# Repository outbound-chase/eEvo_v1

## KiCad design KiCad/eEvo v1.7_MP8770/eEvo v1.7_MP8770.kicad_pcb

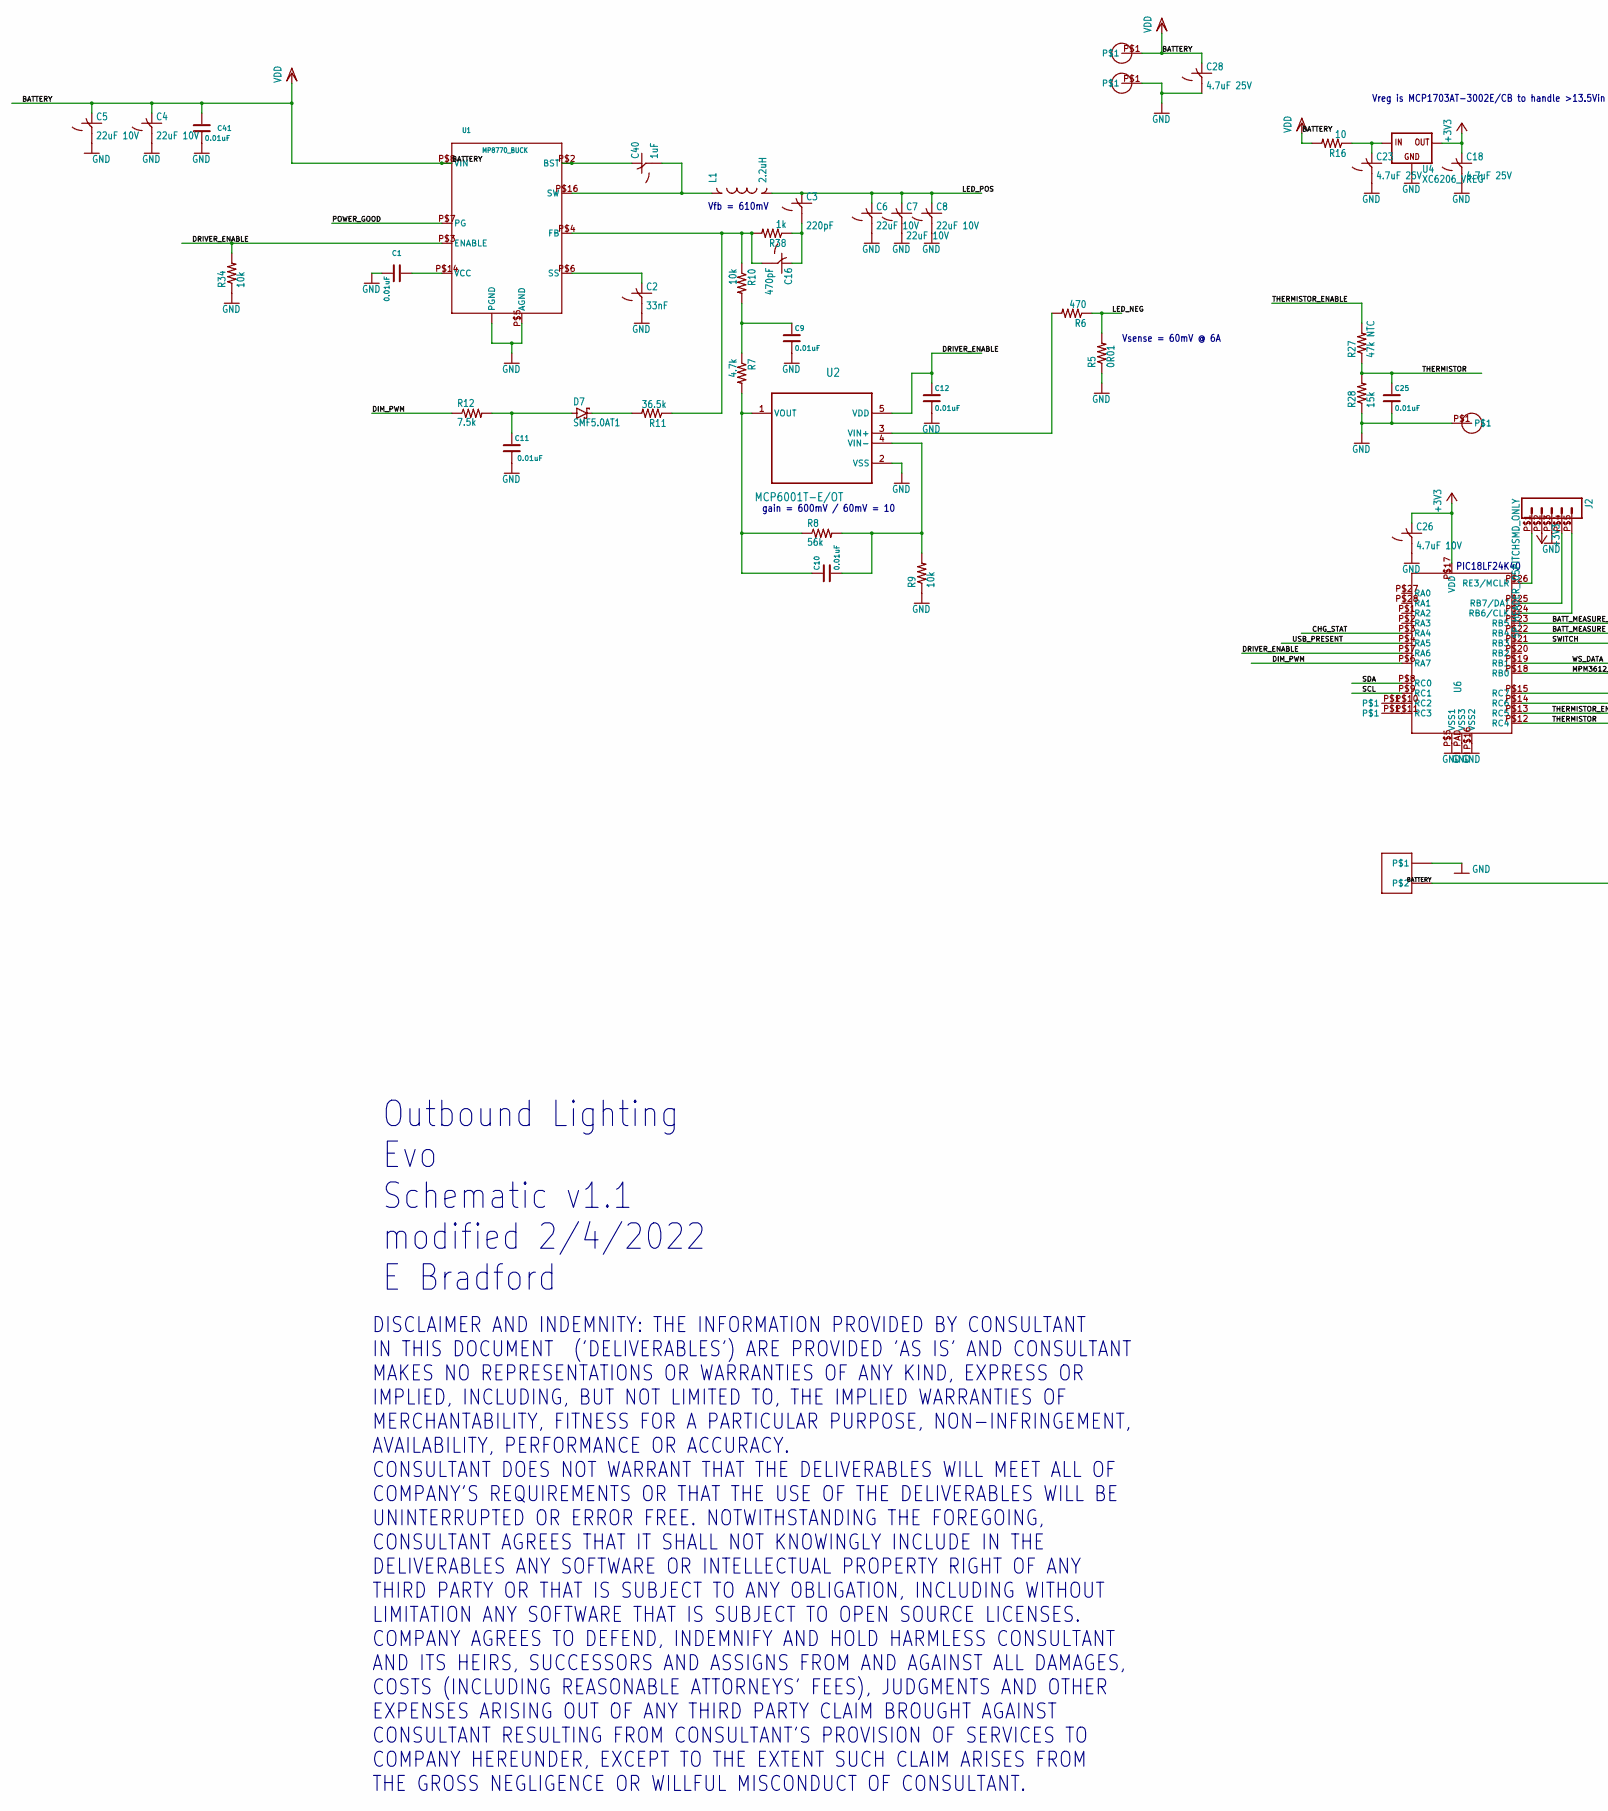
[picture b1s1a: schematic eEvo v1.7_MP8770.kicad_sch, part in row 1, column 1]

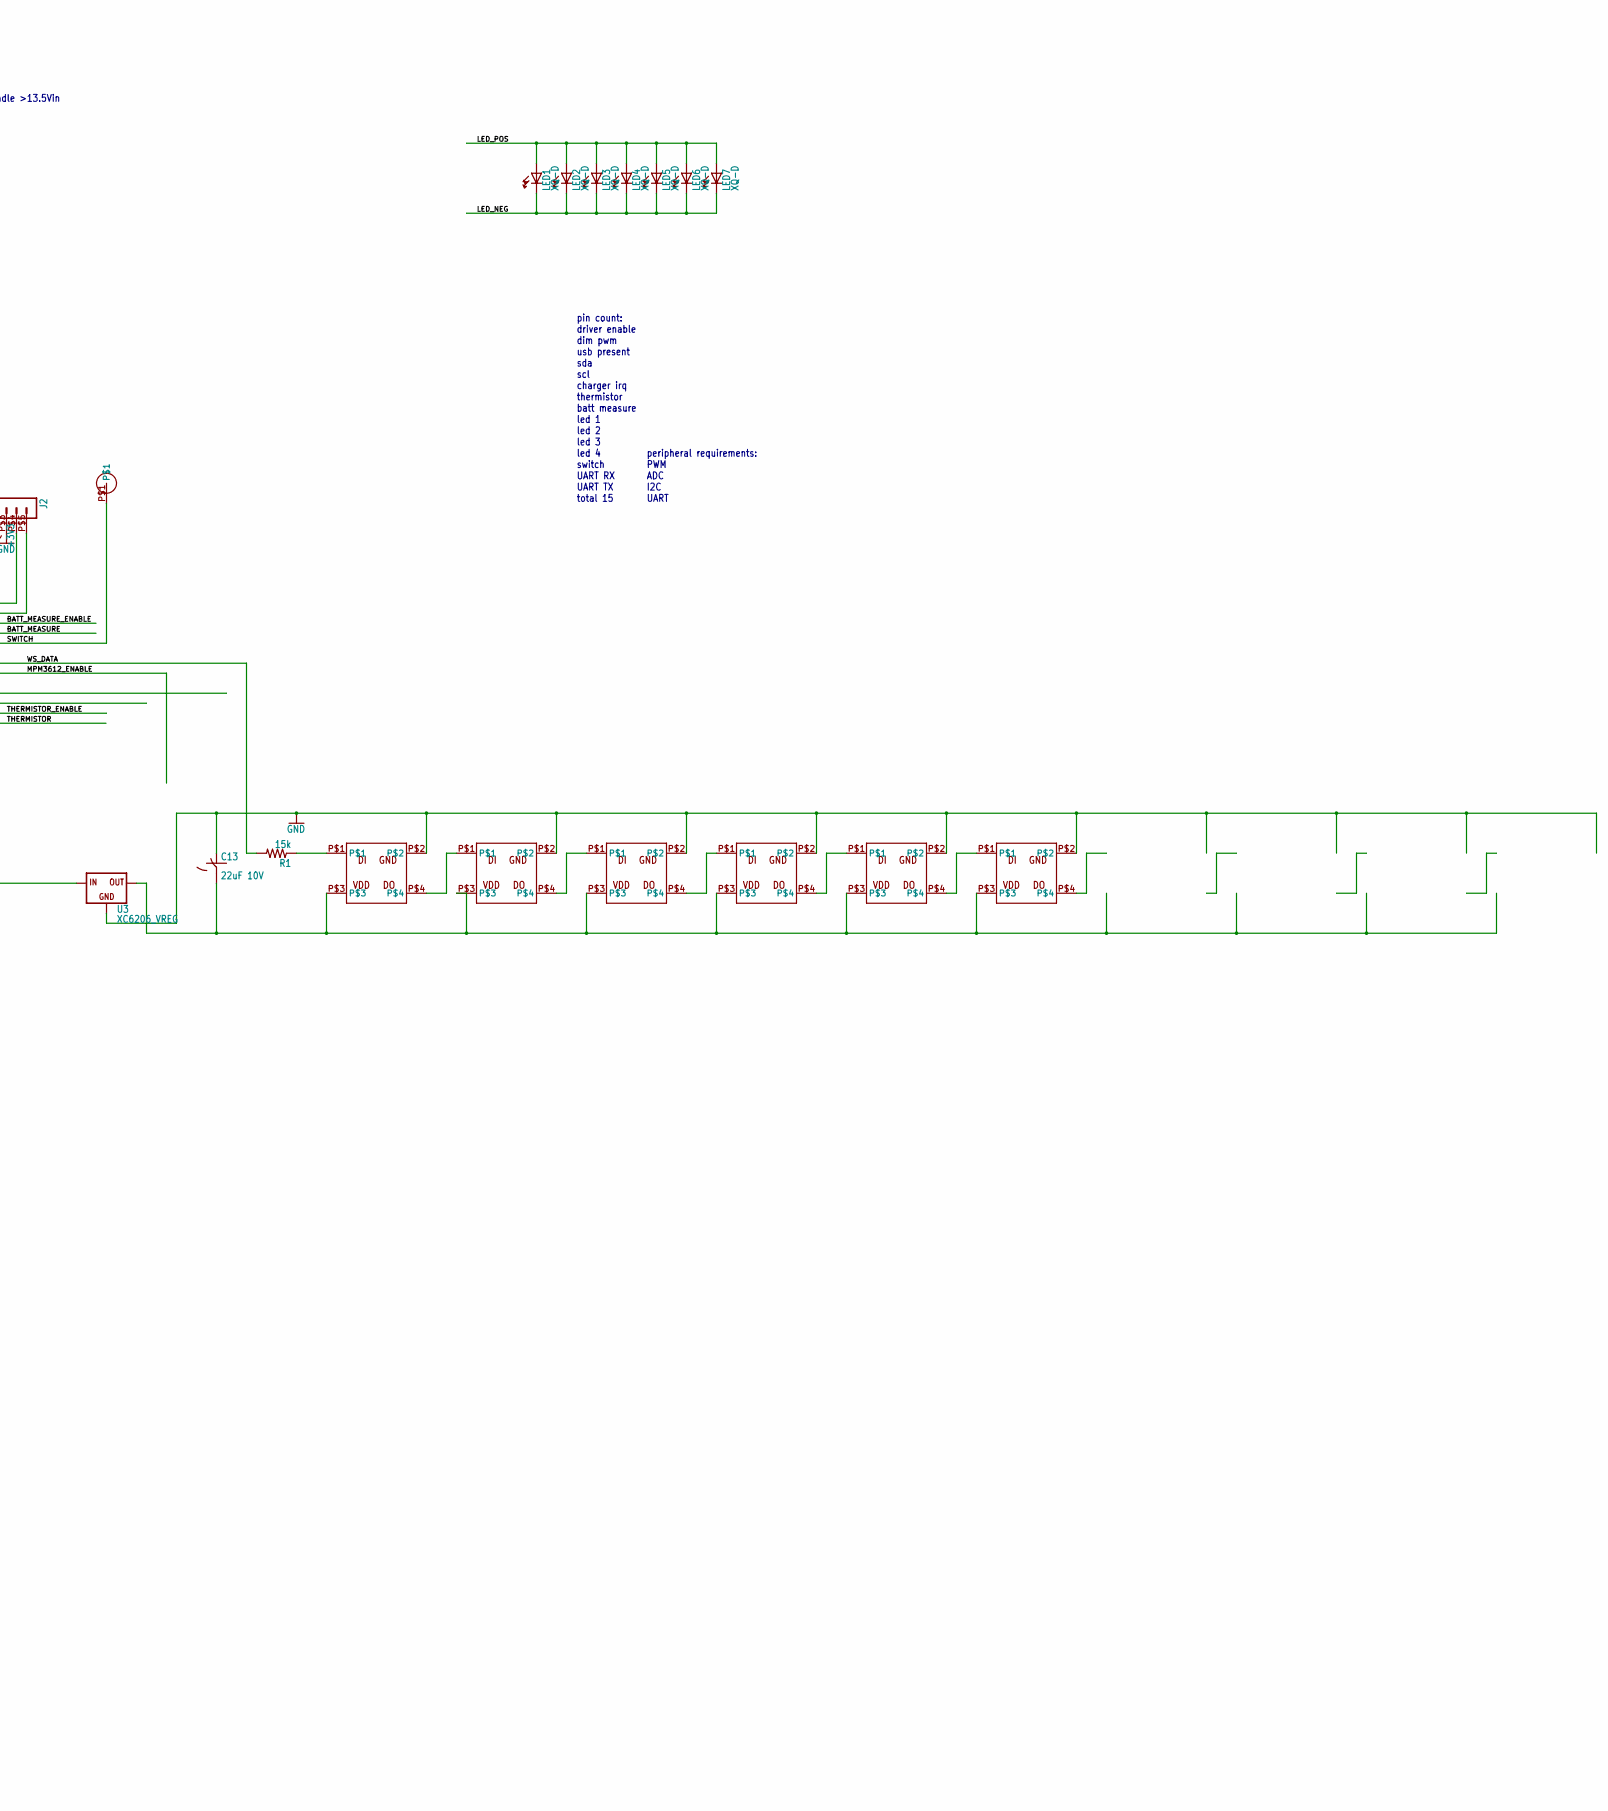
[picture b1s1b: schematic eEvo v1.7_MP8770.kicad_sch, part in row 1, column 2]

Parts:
C1, C9, C10, C11, C12, C25, C41: 0.01uF; C0603_DS; Voltage 25V; Tolerance 10%; MPN Generic
C2: 33nF; C0603
C3: 220pF; C0603
C4, C5, C6, C7, C8, C13: 22uF 10V; C0603
C16: 470pF; C0603
C18, C23, C28: 4.7uF 25V; C0603
C26: 4.7uF 10V; C0603
C40: 1uF; C0603
D7: SMF5.0AT1; SOD123FL
J1: CONN_2-PIN_MOLEX_PICOEZMATE
J2: 5P_HEADER_.05PITCHSMD_ONLY; 5P_ICSP_SMD
L1: 2.2uH; INDUCTOR_5.7X5.2
LED1, LED2, LED3, LED4, LED5, LED6, LED7: XQ-D
R1, R28: 15k; R0603
R5: 0R01; M1206
R6: 470; R0603
R7: 4.7k; R0603
R8: 56k; R0603
R9, R10, R34: 10k; R0603
R11: 36.5k; R0603
R12: 7.5k; R0603
R16: 10; R0603
R27: 47k NTC; R0603
R38: 1k; R0603
RX0: WIREPAD_50MIL
TX0: WIREPAD_50MIL
U1: MP8770_BUCK
U2: MCP6001T-E/OT; SOT95P270X145-5N
U3, U4: XC6206_VREG; SOT-23
U6: PIC18F25K40UQFN_4X4; UQFN-28_4X4
U$2, U$3, U$4, U$5, U$6, U$7: WS2812B-2020
U$12, U$13, U$14, U$15: WIREPAD2X2MM_SQ; PAD_2X2

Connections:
+3V3: C18.1, C26.1, J2.P$2 (2), U4.2 (OUT), U6.P$17 (VDD)
BATTERY: C4.1, C5.1, C28.1, C41.1, J1.P$2, J1.P$3, R16.2, U1.P$8 (VIN), U3.3 (IN), U$14.P$1
BATT_MEASURE: U6.P$22 (RB4)
BATT_MEASURE_ENABLE: U6.P$23 (RB5)
CHG_STAT: U6.P$3 (RA4)
DIM_PWM: R12.1, U6.P$6 (RA7)
DRIVER_ENABLE: C12.1, R34.2, U1.P$3 (ENABLE), U2.5 (VDD), U6.P$7 (RA6)
GND: C1.2, C2.2, C4.2, C5.2, C6.2, C7.2, C8.2, C9.2, C11.2, C12.2, C13.1, C18.2, C23.2, C25.2, C26.2, C28.2, C41.2, J1.P$1, J1.P$4, J2.P$3 (3), R5.1, R9.1, R28.1, R34.1, U1.P$5 (AGND), U1.P$9 (PGND), U1.P$10 (PGND), U1.P$11 (PGND), U1.P$12 (PGND), U1.P$13 (PGND), U2.2 (VSS), U3.1 (GND), U4.1 (GND), U6.P$5 (VSS1), U6.P$16 (VSS2), U6.PAD (VSS3), U$2.P$2, U$3.P$2, U$4.P$2, U$5.P$2, U$6.P$2, U$7.P$2, U$13.P$1, U$15.P$1
LED_NEG: LED1.2 (C), LED2.2 (C), LED3.2 (C), LED4.2 (C), LED5.2 (C), LED6.2 (C), LED7.2 (C), R5.2, R6.1
LED_POS: C3.1, C6.1, C7.1, C8.1, L1.P$2 (2), LED1.1 (A), LED2.1 (A), LED3.1 (A), LED4.1 (A), LED5.1 (A), LED6.1 (A), LED7.1 (A)
MPM3612_ENABLE: U6.P$18 (RB0)
unnamed: C3.2, C16.1, R38.1
unnamed: C40.2, L1.P$1 (1), U1.P$16 (SW)
unnamed: C13.2, U3.2 (OUT), U$2.P$3, U$3.P$3, U$4.P$3, U$5.P$3, U$6.P$3, U$7.P$3
unnamed: C1.1, U1.P$14 (VCC)
unnamed: C2.1, U1.P$6 (SS)
unnamed: R1.1, U$2.P$1
unnamed: C16.2, R10.1, R11.1, R38.2, U1.P$4 (FB)
unnamed: R6.2, U2.3 (VIN+)
unnamed: C10.1, R7.2, R8.1, U2.1 (VOUT)
unnamed: C9.1, R7.1, R10.2
unnamed: C10.2, R8.2, R9.2, U2.4 (VIN-)
unnamed: C11.1, D7.A, R12.2
unnamed: U$2.P$4, U$3.P$1
unnamed: U$3.P$4, U$4.P$1
unnamed: U$4.P$4, U$5.P$1
unnamed: RX0.P$1, U6.P$11 (RC3)
unnamed: U$5.P$4, U$6.P$1
unnamed: U$6.P$4, U$7.P$1
unnamed: TX0.P$1, U6.P$10 (RC2)
unnamed: C23.1, R16.1, U4.3 (IN)
unnamed: J2.P$1 (1), U6.P$26 (RE3/MCLR)
unnamed: D7.C, R11.2
unnamed: J2.P$4 (4), U6.P$25 (RB7/DAT)
unnamed: J2.P$5 (5), U6.P$24 (RB6/CLK)
unnamed: C40.1, U1.P$2 (BST)
POWER_GOOD: U1.P$7 (PG)
SCL: U6.P$9 (RC1)
SDA: U6.P$8 (RC0)
SWITCH: U6.P$21 (RB3), U$12.P$1
THERMISTOR: C25.1, R27.1, R28.2, U6.P$12 (RC4)
THERMISTOR_ENABLE: R27.2, U6.P$13 (RC5)
USB_PRESENT: U6.P$4 (RA5)
WS_DATA: R1.2, U6.P$19 (RB1)

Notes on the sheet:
Outbound Lighting Evo Schematic v1.1 modified 2/4/2022 E Bradford
PIC18LF24K40
DISCLAIMER AND INDEMNITY: THE INFORMATION PROVIDED BY CONSULTANT IN THIS DOCUMENT ('DELIVERABLES') ARE PROVIDED 'AS IS' AND CONSULTANT MAKES NO REPRESENTATIONS OR WARRANTIES OF ANY KIND, EXPRESS OR IMPLIED, INCLUDING, BUT NOT LIMITED TO, THE IMPLIED WARRANTIES OF MERCHANTABILITY, FITNESS FOR A PART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
Vreg is MCP1703AT-3002E/CB to handle >13.5Vin
Vfb = 610mV
Vsense = 60mV @ 6A
gain = 600mV / 60mV = 10
peripheral requirements: PWM ADC I2C UART
pin count: driver enable dim pwm usb present sda scl charger irq thermistor batt measure led 1 led 2 led 3 led 4 switch UART RX UART TX total 15

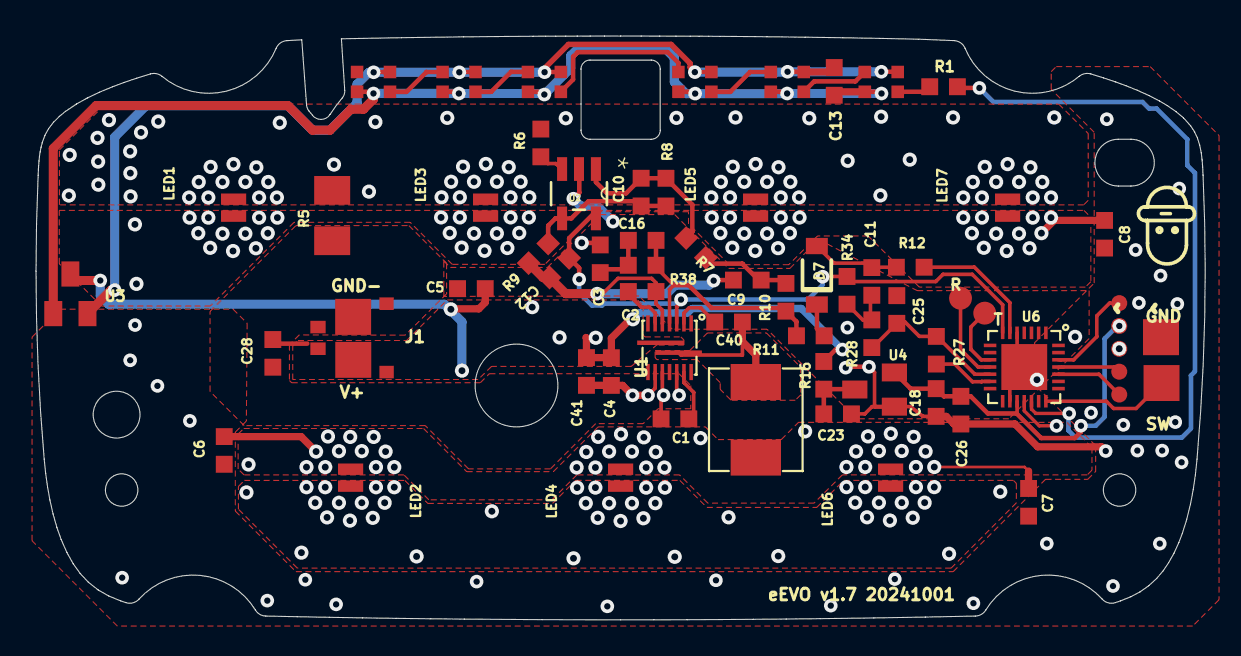
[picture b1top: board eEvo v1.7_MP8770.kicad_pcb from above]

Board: 2 copper layers, 64.9 x 32.4 mm, 63 parts (0 on the bottom side), 36 nets.

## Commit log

2025-03-26 Initial Commit of Eagle Design Files
    Copied .sch and .brd design files from network drives
2025-03-26 Update .gitignore
    Add KiCad ignores
2025-03-26 Added kiCad folder, beginning kicad migration

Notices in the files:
KiCad/eEvo v1.7_MP8770/eEvo v1.7_MP8770.kicad_sch:
LIMITATION ANY SOFTWARE THAT IS SUBJECT TO OPEN SOURCE LICENSES.
